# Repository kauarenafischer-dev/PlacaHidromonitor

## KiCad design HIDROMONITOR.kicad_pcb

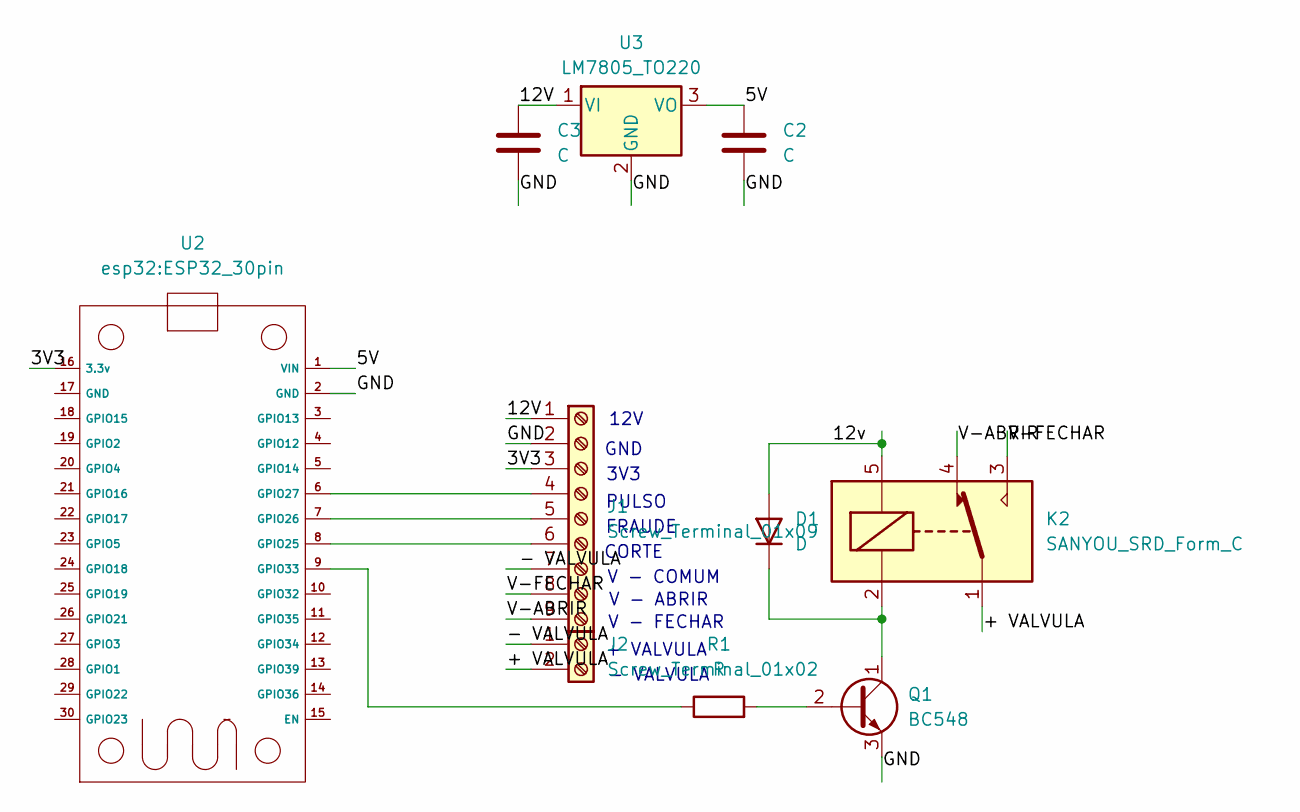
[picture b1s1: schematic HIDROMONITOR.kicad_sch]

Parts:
C2, C3: C; C_Rect_L7.0mm_W2.5mm_P5.00mm
D1: D; D_DO-41_SOD81_P10.16mm_Horizontal
J1: Screw_Terminal_01x09; TerminalBlock_Phoenix_MKDS-1,5-9_1x09_P5.00mm_Horizontal
J2: Screw_Terminal_01x02; TerminalBlock_Phoenix_MKDS-1,5-2_1x02_P5.00mm_Horizontal
K2: SANYOU_SRD_Form_C; Relay_SPDT_SANYOU_SRD_Series_Form_C
Q1: BC548; TO-92
R1: R; R_Axial_DIN0207_L6.3mm_D2.5mm_P7.62mm_Horizontal
U2: ESP32_30pin
U3: LM7805_TO220; TO-220-3_Vertical

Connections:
/3V3: J1.3, U2.16 (3.3v)
/5V: C2.1, U2.1 (VIN), U3.3 (VO)
/12V: C3.1, J1.1, U3.1 (VI)
/+ VALVULA: J2.2, K2.1
/- VALVULA: J1.7, J2.1
/<NO NET>: C2.2, C3.2, D1.2 (A), J1.2, K2.5, Q1.3 (E), U2.2 (GND), U3.2 (GND)
/V-ABRIR: J1.9, K2.4
/V-FECHAR: J1.8, K2.3
unnamed: D1.1 (K), K2.2, Q1.1 (C)
unnamed: J1.4, U2.6 (GPIO27)
unnamed: J1.5, U2.7 (GPIO26)
unnamed: J1.6, U2.8 (GPIO25)
unnamed: Q1.2 (B), R1.2
unnamed: R1.1, U2.9 (GPIO33)

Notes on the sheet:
+ VALVULA
CORTE
12V
GND
PULSO
V - FECHAR
- VALVULA
FRAUDE
V - COMUM
V - ABRIR
3V3

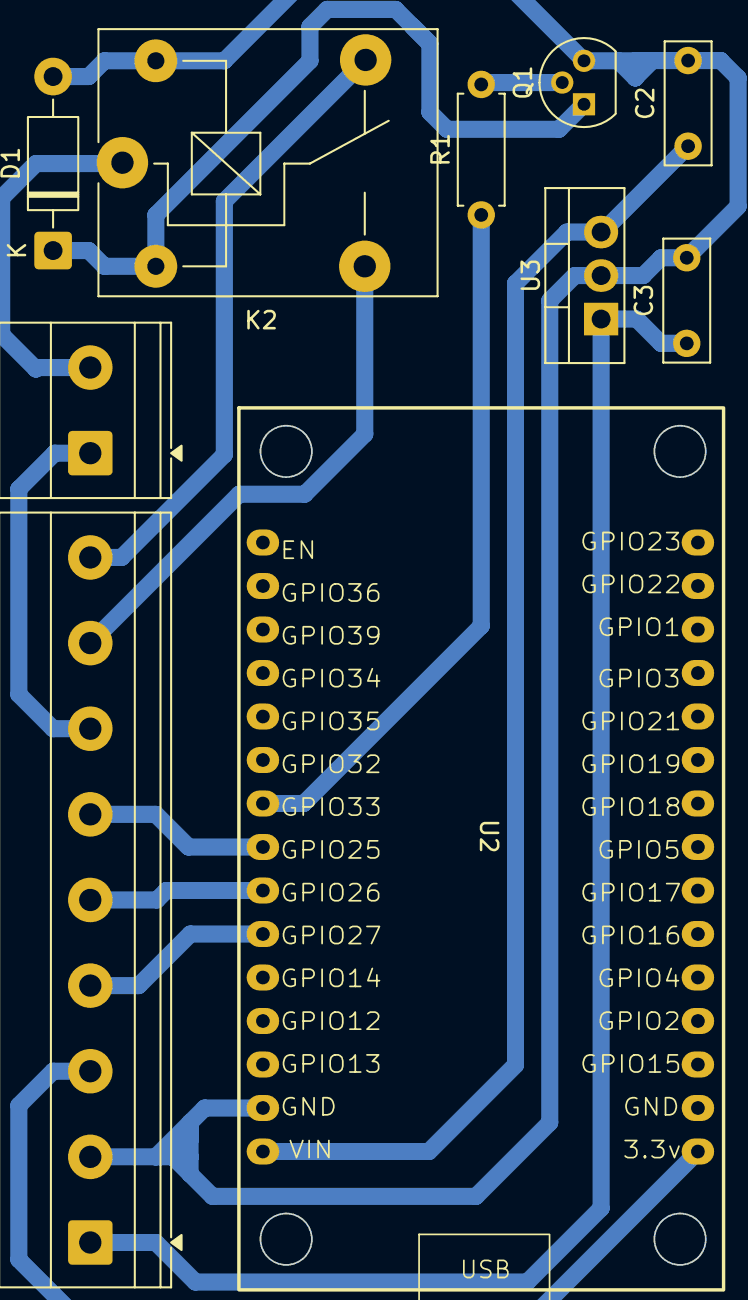
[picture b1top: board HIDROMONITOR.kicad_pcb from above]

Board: 2 copper layers, 10 parts (0 on the bottom side), 14 nets.
